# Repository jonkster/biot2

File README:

Biotz2

This is a new implementation of Biotz stuff - based on lessons learnt from
first Biotz project (see ../biotz)

NB when commiting changes to RIOT do:
git push originNew
('git push' will try and push to the real RIOT repository and you will be
refused).

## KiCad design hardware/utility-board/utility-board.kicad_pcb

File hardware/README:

when designing board in KiCad

1. set origin at suitable point near bottom left of board

2. Plot KiCad board (in Gerber Format)

pcb2gcode
---------

don't use vectorial core (due thickness of cutting tool)

Backside mirroring = Y axis

Milling depth -0.1mm
200 mm/min horiz speed
drill depth -3.0mm
    mill holes, use single bit (0.8mm?)

outline 0.8mm
-2.5mm depth
horiz speed 100mm/min
max single pass depth 1mm

CNC
--------

When first starting up CNC (or if need to drill reference/holding holes in a
fresh PCB)

1. jog Y axis so spindle clear of clamps when X homes

2. Home all axes

3. Set Touch Off on X and Y to initialise starting point (important if drilling
   reference marks for new PCB)

4. bring drill close to work surface and touch off Z   

Tools
-----

Currently using 0.8mm end mill

Milling PCB
-------------

After exporting gcode from pcb2gcode application:

1. load BACK surface gcode

1. jog spindle to suitable point on PCB

2. touch off X and Y (and if necessary bring Z close to surface and touch off Z)
   (may need to rejog at this point to get outline at a suitable point)

3. run BACK gcode (will prompt for auto level probe etc)

4. G0 X0, G0 Y0 to bring drill back to origin and drill a reference hole

5. flip board and load FRONT gcode

6. Jog X until it lines up with the reference hole exactly

7. touch off X

7. run FRONT gcode

8. load and run drill gcode

9. load and run outline gcode

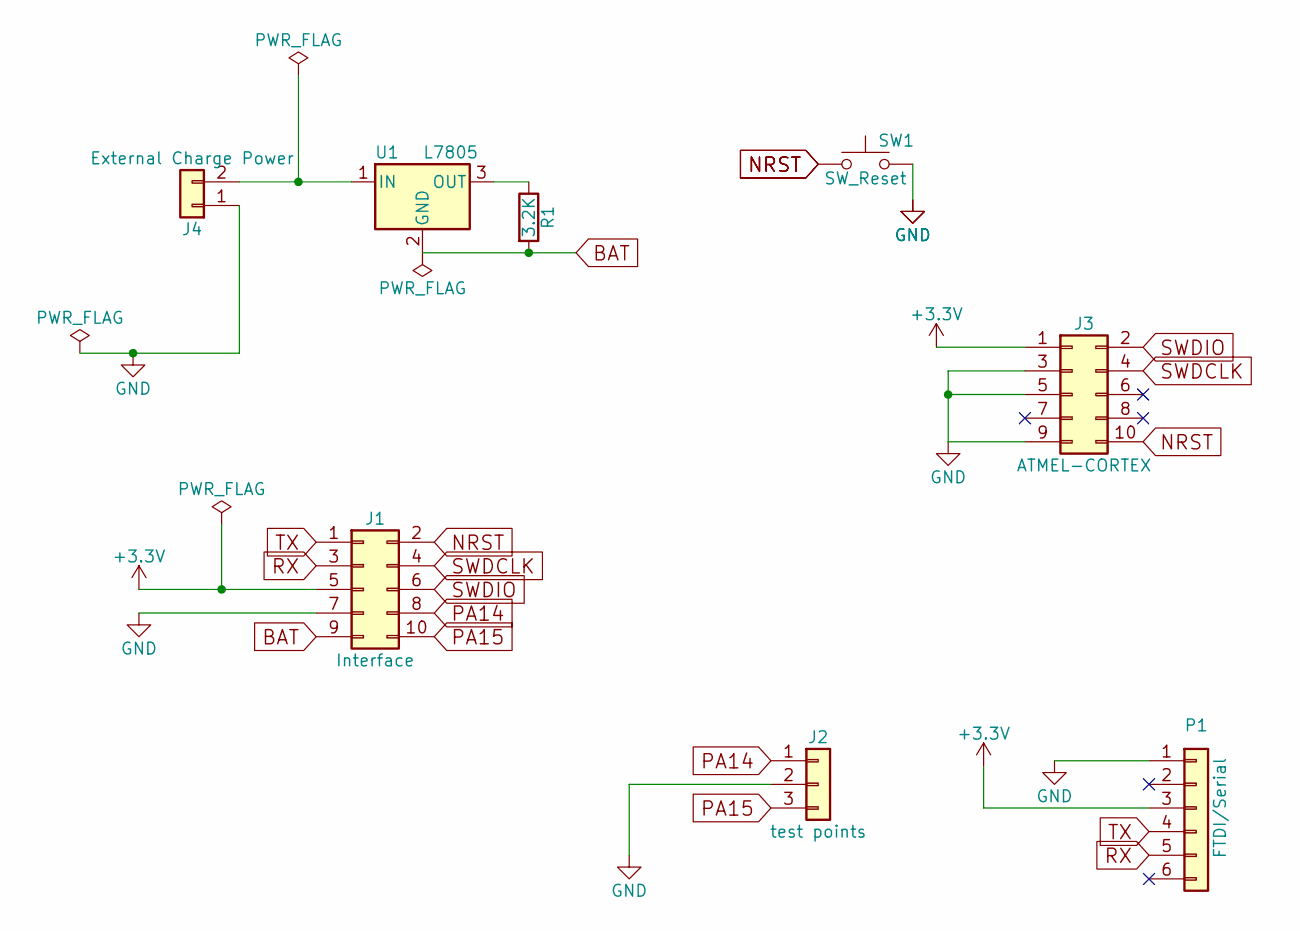
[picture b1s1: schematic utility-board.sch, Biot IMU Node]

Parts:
J1: Interface; Pin_Header_Straight_2x05_Pitch2.54mm_SMD
J2: test points; Pin_Header_Straight_1x03_Pitch2.54mm_SMD_Pin1Right
J3: ATMEL-CORTEX; Pin_Header_Straight_2x05_Pitch1.27mm_SMD
J4: External Charge Power; Pin_Header_Straight_1x02_Pitch2.54mm_SMD_Pin1Right
P1: FTDI/Serial; Pin_Header_Straight_1x06_Pitch2.54mm_SMD_Pin1Right
R1: 3.2K; R_1210
SW1: SW_Reset; SW_SPST_B3S-1000
U1: L7805; TO-263-3_TabPin2

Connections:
+3V3: J1.5, J3.1, P1.3
BAT: J1.9, R1.2, U1.2 (GND)
GND: J1.7, J2.2, J3.3, J3.5, J3.9, J4.1, P1.1, SW1.2
NRST: J1.2, J3.10, SW1.1
unnamed: J4.2, U1.1 (IN)
unnamed: R1.1, U1.3 (OUT)
PA14: J1.8, J2.1
PA15: J1.10, J2.3
RX: J1.3, P1.5
SWDCLK: J1.4, J3.4
SWDIO: J1.6, J3.2
TX: J1.1, P1.4

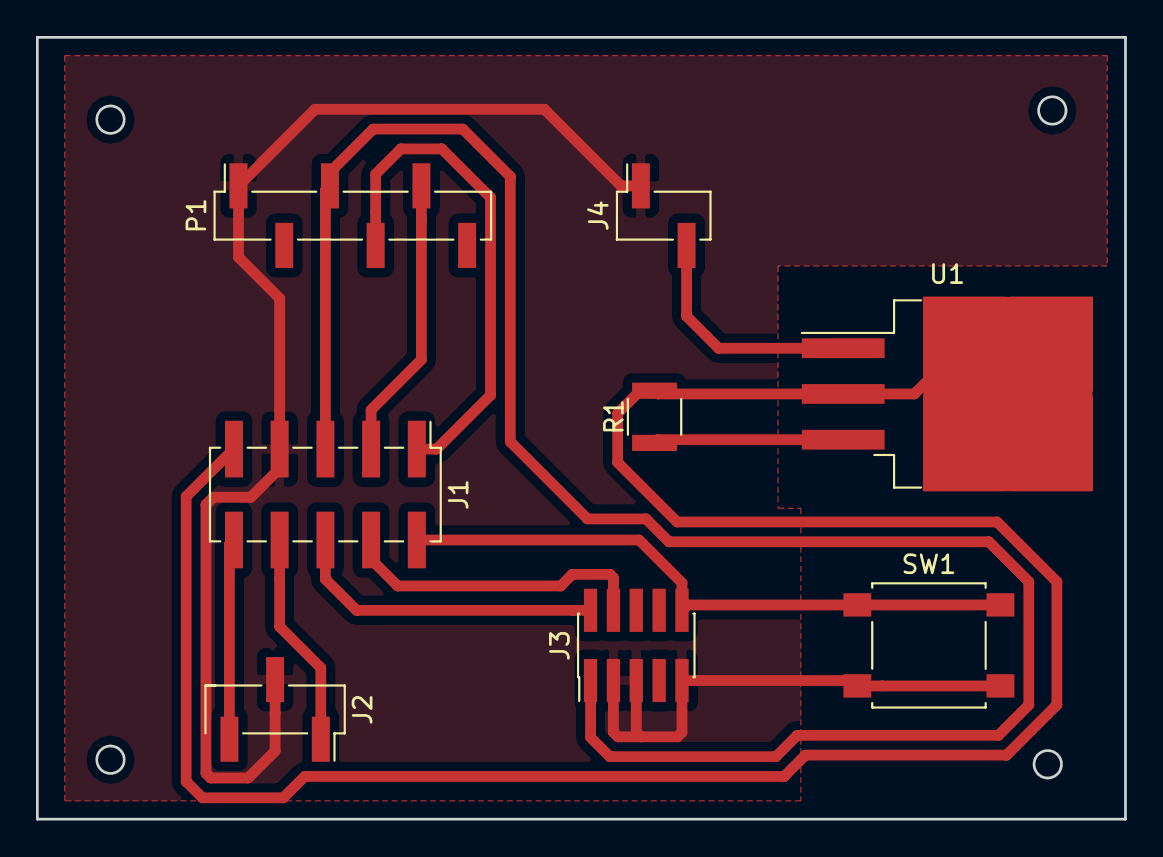
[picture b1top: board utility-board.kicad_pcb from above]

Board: 2 copper layers, 60.5 x 43.4 mm, 8 parts (0 on the bottom side), 12 nets.

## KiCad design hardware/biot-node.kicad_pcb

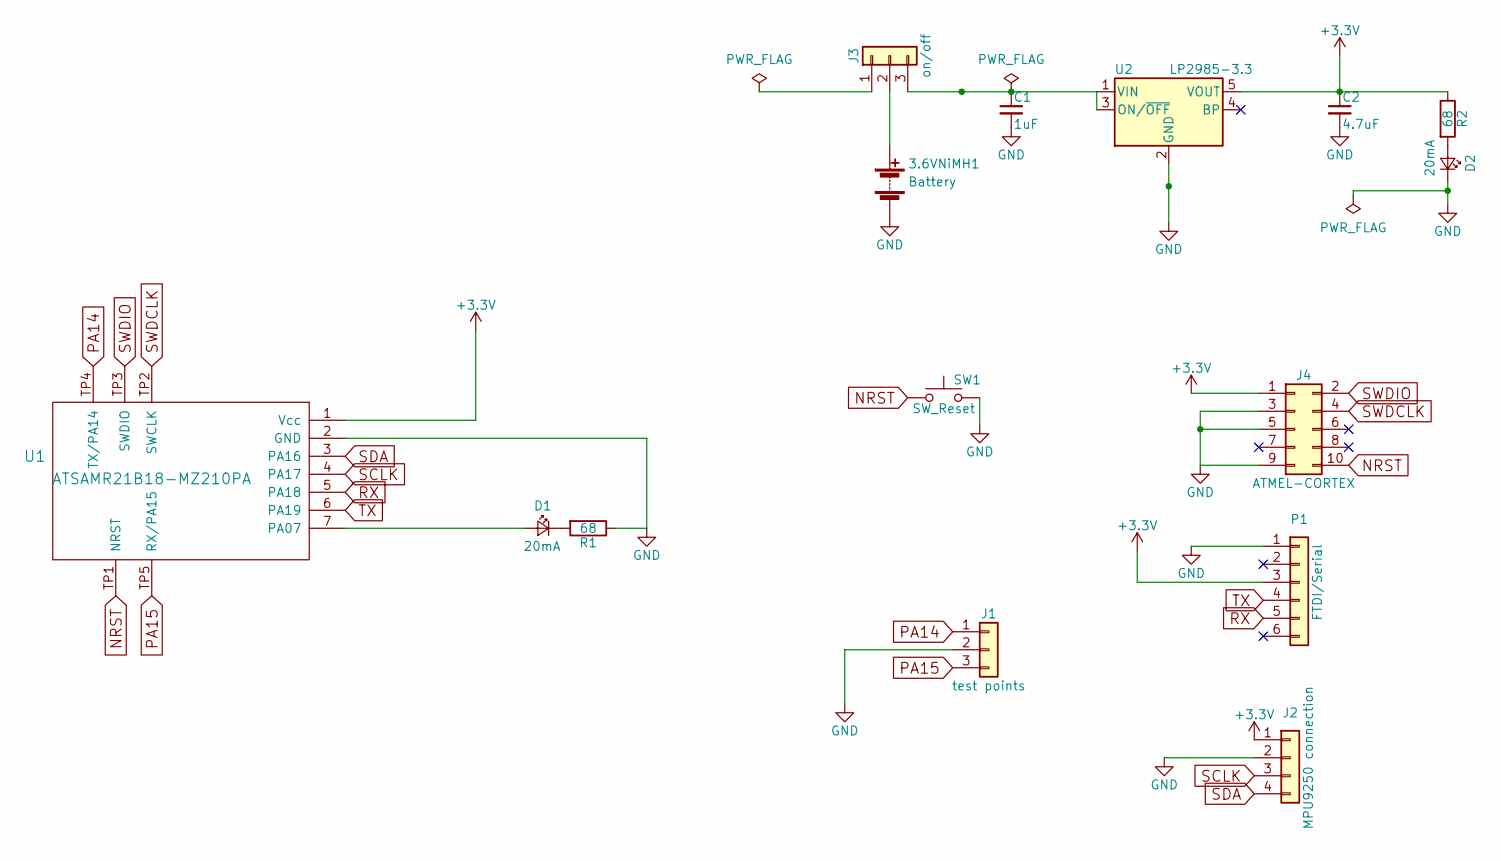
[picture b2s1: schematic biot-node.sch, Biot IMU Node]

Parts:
3.6VNiMH1: Battery; varta3v200h
C1: 1uF; C_1206
C2: 4.7uF; C_1206
D1, D2: 20mA; LED_1206
J1: test points; Pin_Header_Straight_1x03_Pitch2.54mm_SMD_Pin1Right
J2: MPU9250 connection; Pin_Header_Straight_1x04_Pitch2.54mm
J3: on/off; Pin_Header_Straight_1x03_Pitch2.54mm_SMD_Pin1Right
J4: ATMEL-CORTEX; Pin_Header_Straight_2x05_Pitch1.27mm_SMD
P1: FTDI/Serial; Pin_Header_Straight_1x06_Pitch2.54mm_SMD_Pin1Right
R1, R2: 68; R_1210
SW1: SW_Reset; SW_SPST_B3S-1000
U1: ATSAMR21B18-MZ210PA
U2: LP2985-3.3; SOT-23-5

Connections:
+3V3: C2.1, J2.1, J4.1, P1.3, R2.1, U1.1 (Vcc), U2.5 (VOUT)
GND: 3.6VNiMH1.2 (-), C1.2, C2.2, D2.1 (K), J1.2, J2.2, J4.3, J4.5, J4.9, P1.1, R1.1, SW1.2, U1.2 (GND), U2.2 (GND)
NRST: J4.10, SW1.1, U1.TP1 (NRST)
unnamed: 3.6VNiMH1.1 (+), J3.2
unnamed: C1.1, J3.3, U2.1 (VIN), U2.3 (ON/~OFF~)
unnamed: D1.1 (K), R1.2
unnamed: D1.2 (A), U1.7 (PA07)
unnamed: D2.2 (A), R2.2
PA14: J1.1, U1.TP4 (TX/PA14)
PA15: J1.3, U1.TP5 (RX/PA15)
RX: P1.5, U1.5 (PA18)
SCLK: J2.3, U1.4 (PA17)
SDA: J2.4, U1.3 (PA16)
SWDCLK: J4.4, U1.TP2 (SWCLK)
SWDIO: J4.2, U1.TP3 (SWDIO)
TX: P1.4, U1.6 (PA19)

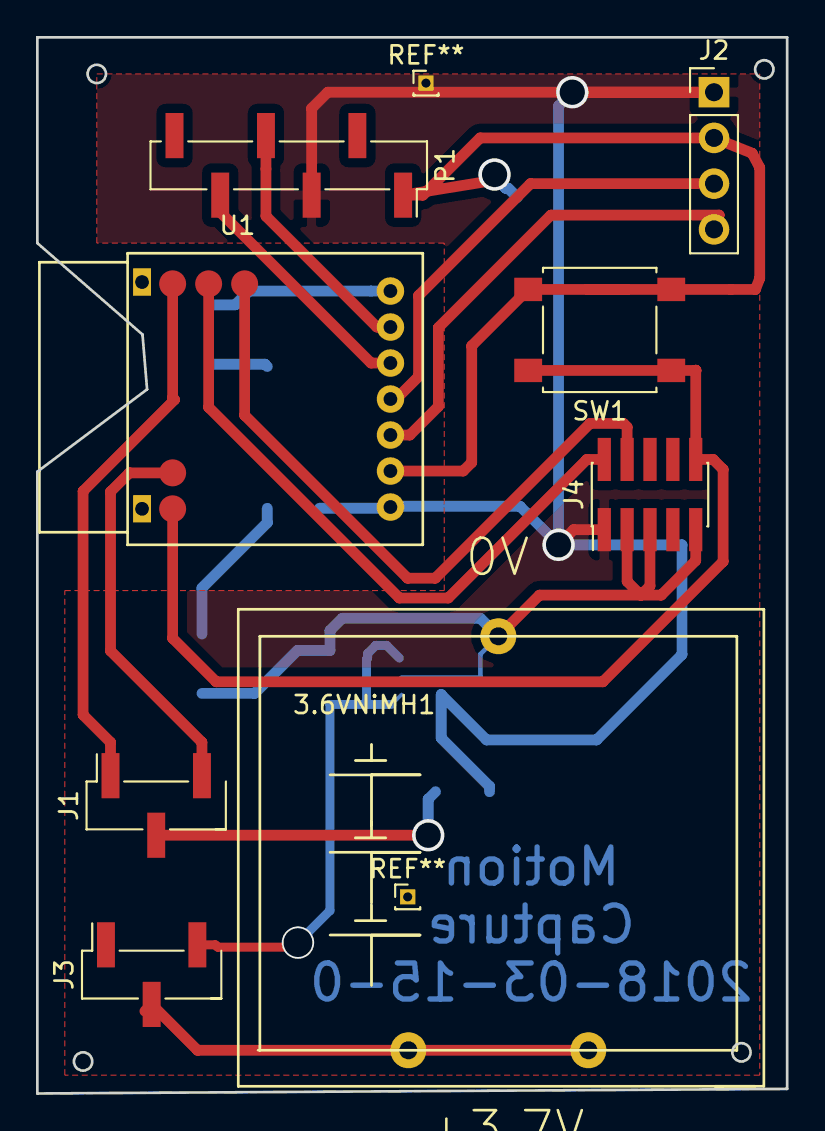
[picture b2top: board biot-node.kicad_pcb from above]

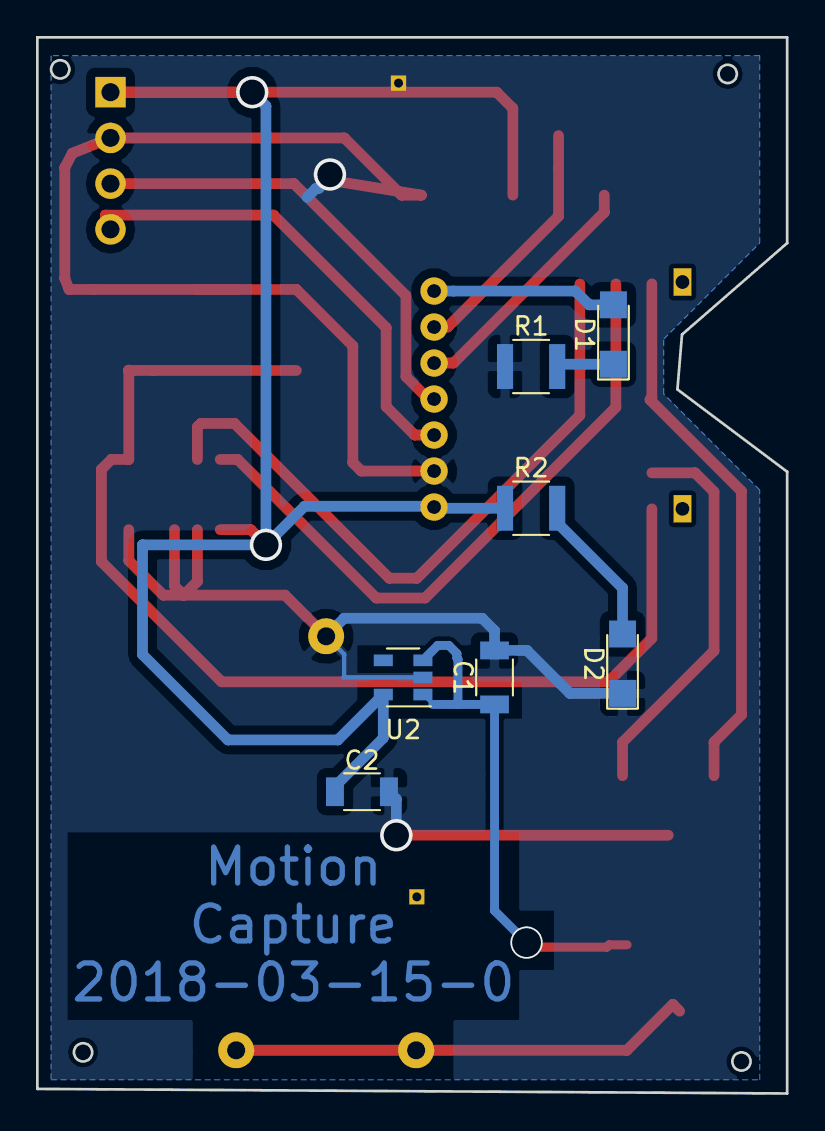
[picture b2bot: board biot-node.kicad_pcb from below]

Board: 2 copper layers, 41.7 x 58.7 mm, 15 parts (7 on the bottom side), 16 nets.

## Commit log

2017-03-19 Initial commit of project.
2017-03-21 Adding border router test code.
2017-03-23 Adding bits to communicate with dodag nodes.
2017-03-23 Added 6lowpan node example/test code.
2017-03-23 Removed unneeded text from Makefile.
2017-03-23 Commited RIOT fork.
2017-03-27 emoved cut and paste copyright for other code.
2017-03-27 Initial commit of Biotz border router code.
2017-03-27 Adding common Biotz device code files.
2017-03-27 Added link to utils.
2017-03-27 Added device example 'common' files and example usage system.
2017-03-28 Adding udp communication features.
2017-03-28 Added RIOT changes.
2017-03-29 Adding simple mechanism to do periodic actions.
2017-03-29 Adding Biotz IMU node application.
2017-03-29 Local changes to RIOT.
2017-03-29 Adding IMU functionality.
2017-03-29 Adding udp test example.
2017-03-30 Implementing IMU functionality.
2017-03-30 Rewritten to use new periodic action scheduler.
2017-03-30 Fixed time setting bug due overflowing integers.
2017-04-19 Adding biot user interface node viewing functionality.
2017-04-19 Minor tidying up device code.
2017-04-19 Added ability to throttle requests if router not responding.
2017-04-19 Added missing user interface components.
2017-04-19 Adding more missing user interface components.
2017-04-19 Adding missing user interface components.
2017-05-31 Major changes - moving to better structure.
2017-05-31 Removed old directory.
2017-05-31 Adding node dialogs.
2017-06-01 Adding recording and charting functionality.
2017-06-01 Adding missing utils files.
2017-06-02 Enhanced functionality of system status page.
2017-06-07 Fixed mirrored X axis bug.
2017-06-07 Added Fourier Spectral analysis of recorded data.
2017-06-07 Updated RIOT to latest source.
2017-06-29 Developing recording functionality.
2017-09-14 Added calibration robot code.
2017-09-14 Fixed bug with nodes disappearing on page change and working on recording functionality
2017-09-15 Numerous changes to include untracked additions, streamlining of animation frame use and display of three drawing performance etc.
2017-09-19 Changes to allow nodes to be dropped when dead - work in progress.
2017-09-20 Attempts to improve speed.
2017-09-20 Trying to reduce stuttering.
2017-09-21 Added test code for seperated node and edge components to increase ability to handle request volume.
2017-09-22 Working on increasing performance.
2017-09-22 Working at increasing speed.
2017-09-28 Changes to allow application to search addresses for a biot router.
2017-09-28 Numerous changes to improve bandwidth and stop node data loss.
2017-10-04 Trying to isolate router crash issue.
2017-10-04 Trying to isolate router crash bug.
2017-10-09 Numerous changes to try and get bandwidth and device stability increased.
2017-10-10 Moving work done by edge router to broker to increase performance.
2017-11-08 Setting up new Edge Router System.
2017-11-08 Updating Biot Broker System to be more generic.
2017-11-08 Working at making broker more host generic.
2017-11-09 Developing ability to attach nodes to models of limbs.
2017-11-15 Moving towards ability to define limb assemblies.
2017-11-23 Adding hardware fabrication files.
2017-11-23 New versions of PCB design.
2017-11-24 Modifying PCB to suit my fabrication tools.
2017-11-24 Latest PCB files.
2017-11-24 Added Latest PCB fabrication settings.
2017-11-24 Working on limb assembly stuff.
2017-11-28 Fixing bug with child limbs rotating with parent.
2017-11-29 Adding dummy router for testing purposes.
2017-11-29 Working on better limb assembly interface and detection of environment.
2017-11-29 Adding ability to adjust initial orientation of limb.
2017-11-30 More work on limb assembly.
2017-12-04 Added ability to set a rotation correction for a node (eg if device is mounted at an angle).
2017-12-06 Refactoring biot service to new biot broker service.
2017-12-08 COntinuining to refactor to a simpler set of components.
2017-12-08 Continuing refactor to simpler components.
2017-12-12 Continuing refactor.
2017-12-14 More refactor.
2017-12-15 Fixing bugs with refactor when using real biot nodes.
2017-12-15 Fixing limb assembly issues due refactor.
2018-01-02 Working on issues with latest nodes not joining 6lowpan network.
2018-01-15 Fixed problem with node not joining DODAG.
2018-01-31 Adding lost stashed code for compressing biot messages.
2018-01-31 Fixing network discory broadcast mechanism.
2018-01-31 Removed unwanted log file.
2018-01-31 Removed diagnostic output.
2018-01-31 Commiting RIOT changes.
2018-02-01 Updating README.
2018-02-01 Removed debug setting.
2018-02-01 Added code for biot nodes to use MPU9255 IMU devices.
2018-02-23 Added ability to compile for either MPU9250 or MPU9255.
2018-02-23 Adding latest biot node circuits.
2018-02-23 Removed unwanted files.
2018-03-02 Improving error logging and general logging for erbridge.
2018-03-06 Modified to use local network prefix when hunting for the broker.
2018-03-14 Hardware with CR123 battery holder.
2018-04-10 Make MPU 9255 standard IMU unit.
2018-04-10 Allow removal of all nodes from broker memory and then a re-read.
2018-04-10 Newer node hardware construction.
2018-04-10 Working on getting assembly of limbs working.
2018-04-10 Setting up new hardware construction/pcb setup.
2018-04-12 Adding 'trails' of movement.
2018-05-15 Adding simpler initialisation to git.
2018-05-16 Improving stability of biot nodes.
2018-05-24 Fixing movement trail drawing.
